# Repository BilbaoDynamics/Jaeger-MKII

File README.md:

# Jaeger MKII

## What's this?

An open source Micro rover robot

## License

GPL license or Creative Commons Attribution-shareAlike (Copyleft)

![license] (http://es.creativecommons.org/blog/wp-content/uploads/2013/04/by-sa_petit.png)

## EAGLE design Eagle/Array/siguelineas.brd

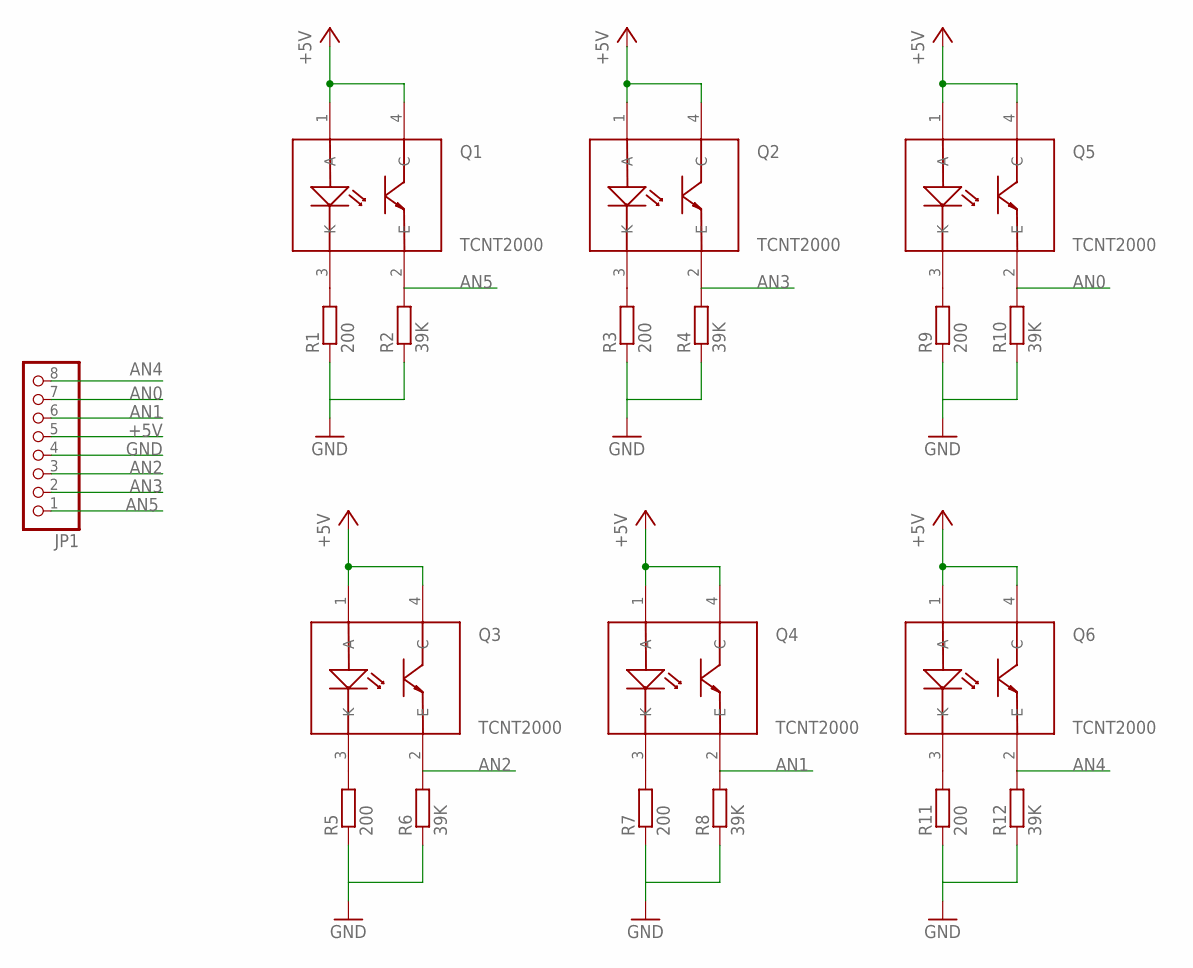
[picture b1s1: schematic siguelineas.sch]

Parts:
JP1: PINHD-1X8; 1X08
Q1, Q2, Q3, Q4, Q5, Q6: TCNT2000; SMD
R1, R3, R5, R7, R9, R11: 200; R0805
R2, R4, R6, R8, R10, R12: 39K; R0805

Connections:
+5V: JP1.5, Q1.1 (A), Q1.4 (C), Q2.1 (A), Q2.4 (C), Q3.1 (A), Q3.4 (C), Q4.1 (A), Q4.4 (C), Q5.1 (A), Q5.4 (C), Q6.1 (A), Q6.4 (C)
AN0: JP1.7, Q5.2 (E), R10.2
AN1: JP1.6, Q4.2 (E), R8.2
AN2: JP1.3, Q3.2 (E), R6.2
AN3: JP1.2, Q2.2 (E), R4.2
AN4: JP1.8, Q6.2 (E), R12.2
AN5: JP1.1, Q1.2 (E), R2.2
GND: JP1.4, R1.1, R2.1, R3.1, R4.1, R5.1, R6.1, R7.1, R8.1, R9.1, R10.1, R11.1, R12.1
unnamed: Q1.3 (K), R1.2
unnamed: Q2.3 (K), R3.2
unnamed: Q3.3 (K), R5.2
unnamed: Q4.3 (K), R7.2
unnamed: Q5.3 (K), R9.2
unnamed: Q6.3 (K), R11.2

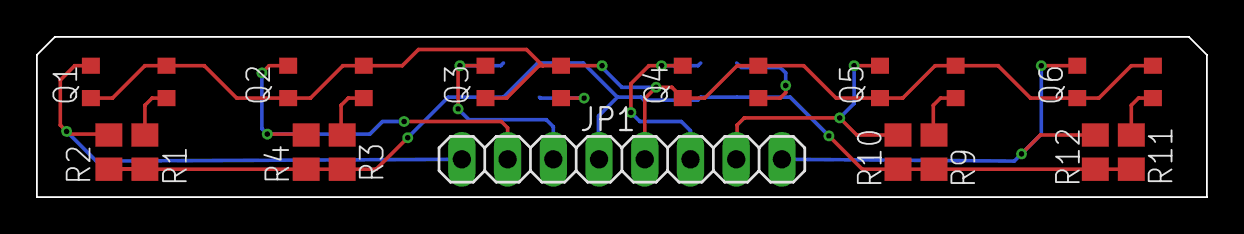
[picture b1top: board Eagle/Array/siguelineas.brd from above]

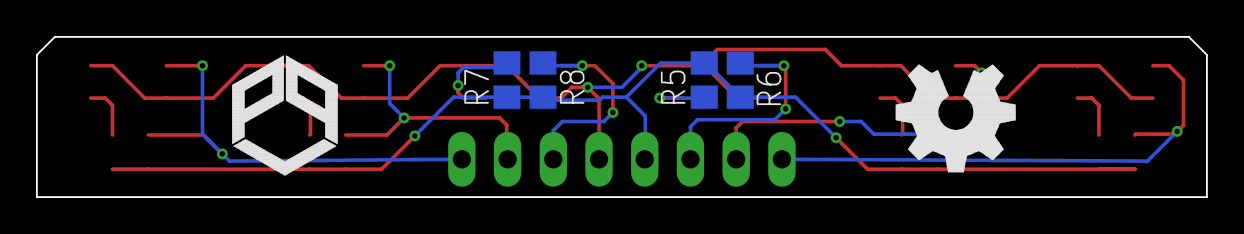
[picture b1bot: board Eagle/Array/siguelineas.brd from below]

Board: 2 copper layers, 65.0 x 8.9 mm, 19 parts (4 on the bottom side), 14 nets.

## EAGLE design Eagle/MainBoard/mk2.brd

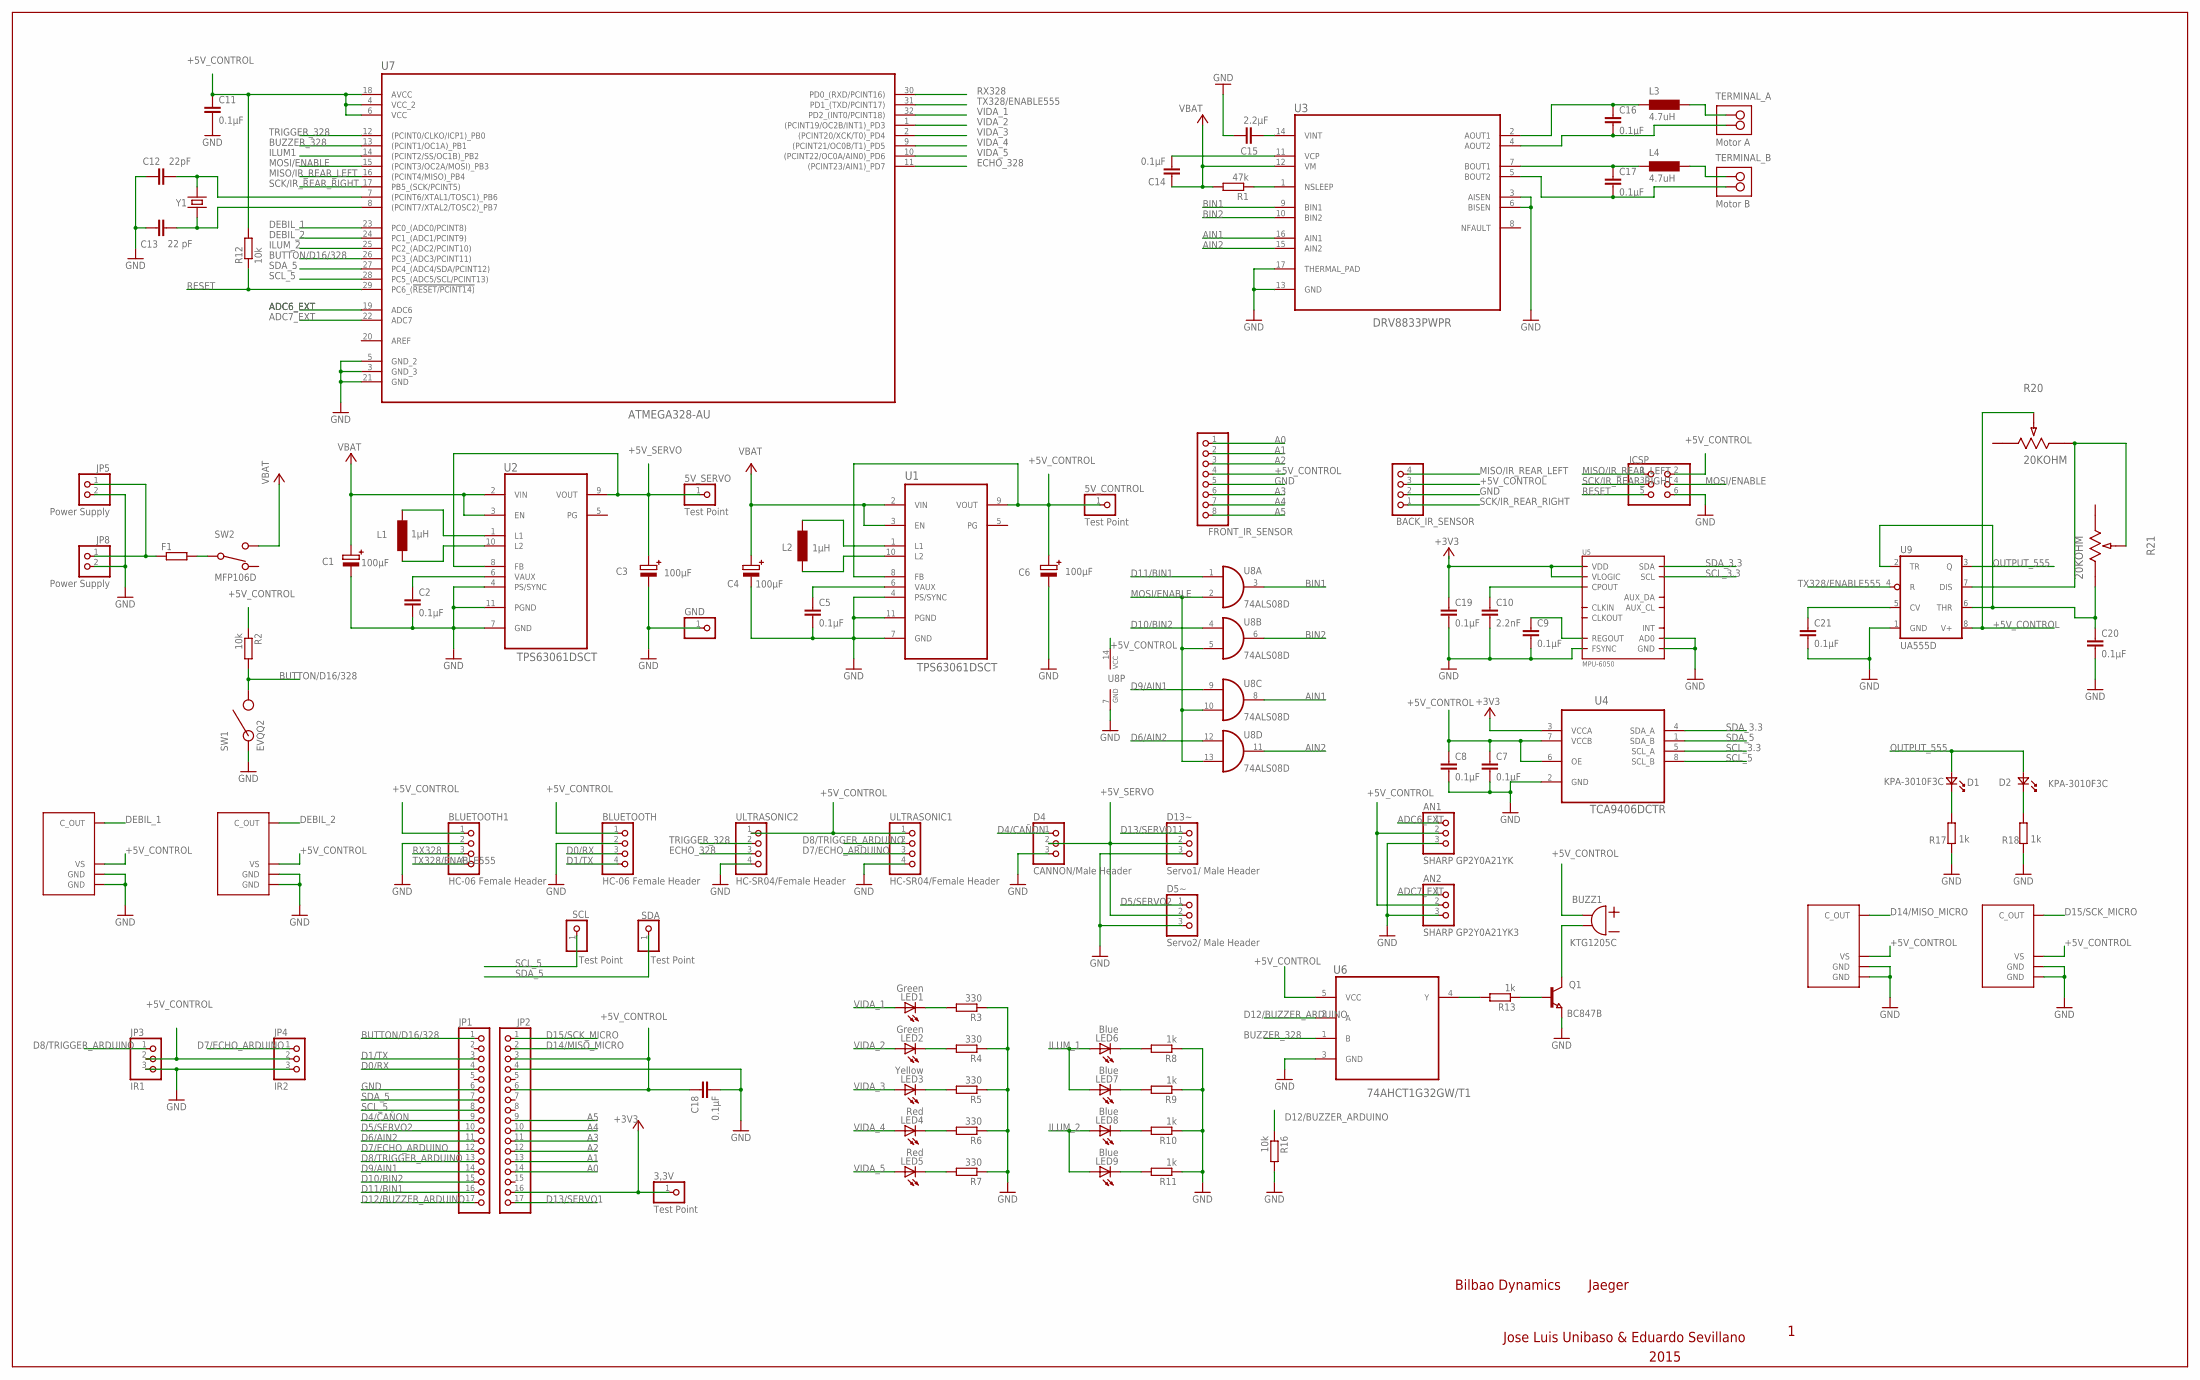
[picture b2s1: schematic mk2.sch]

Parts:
3,3V, 5V_CONTROL, 5V_SERVO: Test Point; 1X01
AN1: SHARP GP2Y0A21YK; 1X03
AN2: SHARP GP2Y0A21YK3; 1X03
BACK_IR_SENSOR: PINHD-1X4; 1X04
BLUETOOTH, BLUETOOTH1: HC-06 Female Header; 1X04
BUZZ1: KTG1205C
C1, C3, C4, C6: 100µF; EDK107M016A9G
C2, C5, C11: 0.1µF; C0805K
C7, C8, C9, C14, C16, C17, C18, C19, C20, C21: 0.1µF; C0805
C10: 2.2nF; C0805
C12: 22pF; C0805K
C13: 22 pF; C0805K
C15: 2.2µF; C0805
D1, D2: KPA-3010F3C
D4: CANNON/Male Header; 1X03
D5~: Servo2/ Male Header; 1X03
D13~: Servo1/ Male Header; 1X03
F1: R-EU_R1206; R1206
FRONT_IR_SENSOR: PINHD-1X8; 1X08
GND: PINHD-1X1; 1X01
ICSP: PINHD-2X3; 2X03
IR_REC1, IR_REC2, IR_REC3, IR_REC4: TSMP77000TR
JP1, JP2: PINHD-1X17; 1X17
JP3: IR1; 1X03
JP4: IR2; 1X03
JP5, JP8: Power Supply; 1X02
L1, L2: 1µH; MCSDRH73B
L3, L4: 4.7uH; SRN4012T-4R7M
LED1, LED2: Green; SML0805
LED3: Yellow; SML0805
LED4, LED5: Red; SML0805
LED6, LED7, LED8, LED9: Blue; SML0805
Q1: BC847B; SOT23
R1: 47k; R0805
R2, R12, R16: 10k; R0805
R3, R4, R5, R6, R7: 330; R0805
R8, R9, R10, R11, R13, R17, R18: 1k; R0805
R20, R21: 20KOHM; POT_EVM2N
SCL: Test Point; 1X01
SDA: Test Point; 1X01
SW1: EVQQ2
SW2: MFP106D
TERMINAL_A: Motor A; CTB30512BK
TERMINAL_B: Motor B; CTB30512BK
U1, U2: TPS63061DSCT; SON50P300X300X80-11N
U3: DRV8833PWPR; SOP65P640X120-17N
U4: TCA9406DCTR; SOP65P400X130-8N
U5: MPU-6050; QFN.24.4X4
U6: 74AHCT1G32GW/T1; SOT65P210X110-5N
U7: ATMEGA328-AU; QFP80P900X900X120-32N
U8: 74ALS08D; SO14
U9: UA555D; SO08
ULTRASONIC1, ULTRASONIC2: HC-SR04/Female Header; 1X04
Y1: E3SB16.0000F09G11AE; E3SB16.0000F09G11A

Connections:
+3V3: 3,3V.1, JP2.16, U4.3 (VCCA)
+5V_CONTROL: 5V_CONTROL.1, AN1.2, AN2.2, BACK_IR_SENSOR.3, BLUETOOTH.1, BLUETOOTH1.1, BUZZ1.+, C6.1, C7.1, C8.1, C11.1, C18.1, FRONT_IR_SENSOR.4, ICSP.2, IR_REC1.2 (VS), IR_REC2.2 (VS), IR_REC3.2 (VS), IR_REC4.2 (VS), JP2.3, JP2.6, JP3.2, JP4.2, R2.1, R12.2, R20.2, U1.8 (FB), U1.9 (VOUT), U4.6 (OE), U4.7 (VCCB), U6.5 (VCC), U7.4 (VCC_2), U7.6 (VCC), U7.18 (AVCC), U8.14 (VCC), U9.8 (V+), ULTRASONIC1.1, ULTRASONIC2.1
+5V_SERVO: 5V_SERVO.1, C3.1, D4.2, D5~.2, D13~.2, U2.8 (FB), U2.9 (VOUT)
A0: FRONT_IR_SENSOR.1, JP2.14
A1: FRONT_IR_SENSOR.2, JP2.13
A2: FRONT_IR_SENSOR.3, JP2.12
A3: FRONT_IR_SENSOR.6, JP2.11
A4: FRONT_IR_SENSOR.7, JP2.10
A5: FRONT_IR_SENSOR.8, JP2.9
ADC6_EXT: AN1.1, U7.19 (ADC6)
ADC7_EXT: AN2.1, U7.22 (ADC7)
AIN1: U3.16 (AIN1), U8.8 (O)
AIN2: U3.15 (AIN2), U8.11 (O)
AM1: L3.P$2, TERMINAL_A.1
BIN1: U3.9 (BIN1), U8.3 (O)
BIN2: U3.10 (BIN2), U8.6 (O)
BM1: L4.P$2, TERMINAL_B.1
BUTTON/D16/328: JP1.1, R2.2, SW1.P$1, SW1.P$4, U7.26 (PC3_(ADC3/PCINT11))
BUZZER_328: U6.1 (B), U7.13 ((PCINT1/OC1A)_PB1)
C14: C13.2, U7.8 ((PCINT7/XTAL2/TOSC2)_PB7), Y1.1
D0/RX: BLUETOOTH.3, JP1.4
D1/TX: BLUETOOTH.4, JP1.3
D2: D2.C, R18.1
D4/CAÑON: D4.1, JP1.9
D5/SERVO2: D5~.1, JP1.10
D6/AIN2: JP1.11, U8.12 (I0)
D7/ECHO_ARDUINO: JP1.12, JP4.1, ULTRASONIC1.3
D8/TRIGGER_ARDUINO: JP1.13, JP3.1, ULTRASONIC1.2
D9/AIN1: JP1.14, U8.9 (I0)
D10/BIN2: JP1.15, U8.4 (I0)
D11/BIN1: JP1.16, U8.1 (I0)
D12/BUZZER_ARDUINO: JP1.17, R16.1, U6.2 (A)
D13/SERVO1: D13~.1, JP2.17
D14/MISO_MICRO: IR_REC1.3 (C_OUT), JP2.2
D15/SCK_MICRO: IR_REC2.3 (C_OUT), JP2.1
DEBIL_1: IR_REC3.3 (C_OUT), U7.23 (PC0_(ADC0/PCINT8))
DEBIL_2: IR_REC4.3 (C_OUT), U7.24 (PC1_(ADC1/PCINT9))
ECHO_328: U7.11 ((PCINT23/AIN1)_PD7), ULTRASONIC2.3
GND: AN1.3, AN2.3, BACK_IR_SENSOR.2, BLUETOOTH.2, BLUETOOTH1.2, C1.2, C2.2, C3.2, C4.2, C5.2, C6.2, C7.2, C8.2, C9.2, C10.2, C11.2, C12.1, C13.1, C15.1, C18.2, C19.2, C20.2, C21.2, D4.3, D5~.3, D13~.3, FRONT_IR_SENSOR.5, GND.1, ICSP.6, IR_REC1.1 (GND), IR_REC1.4 (GND), IR_REC2.1 (GND), IR_REC2.4 (GND), IR_REC3.1 (GND), IR_REC3.4 (GND), IR_REC4.1 (GND), IR_REC4.4 (GND), JP1.6, JP2.4, JP3.3, JP4.3, JP5.2, JP8.2, Q1.2 (E), R3.1, R4.1, R5.1, R6.1, R7.1, R8.1, R9.1, R10.1, R11.1, R16.2, R17.2, R18.2, SW1.P$2, SW1.P$3, U1.4 (PS/SYNC), U1.7 (GND), U1.11 (PGND), U2.4 (PS/SYNC), U2.7 (GND), U2.11 (PGND), U3.3 (AISEN), U3.6 (BISEN), U3.13 (GND), U3.17 (THERMAL_PAD), U4.2 (GND), U5.9 (AD0), U5.11 (FSYNC), U5.18 (GND), U6.3 (GND), U7.3 (GND_3), U7.5 (GND_2), U7.21 (GND), U8.7 (GND), U9.1 (GND), ULTRASONIC1.4, ULTRASONIC2.4
ILUM1: U7.14 ((PCINT2/SS/OC1B)_PB2)
ILUM_1: LED6.A, LED7.A
ILUM_2: LED8.A, LED9.A, U7.25 (PC2_(ADC2/PCINT10))
LED4: LED4.C, R6.2
MISO/IR_REAR_LEFT: BACK_IR_SENSOR.4, ICSP.1, U7.16 ((PCINT4/MISO)_PB4)
MOSI/ENABLE: ICSP.4, U7.15 ((PCINT3/OC2A/MOSI)_PB3), U8.2 (I1), U8.5 (I1), U8.10 (I1), U8.13 (I1)
unnamed: C16.1, L3.P$1, U3.2 (AOUT1)
unnamed: C16.2, TERMINAL_A.2, U3.4 (AOUT2)
unnamed: C17.1, L4.P$1, U3.7 (BOUT1)
unnamed: C17.2, TERMINAL_B.2, U3.5 (BOUT2)
unnamed: C19.1, U5.8 (VLOGIC), U5.13 (VDD)
unnamed: F1.1, JP5.1, JP8.1
unnamed: R1.1, U3.1 (NSLEEP)
unnamed: C14.2, U3.11 (VCP)
unnamed: L2.2, U1.1 (L1)
unnamed: C2.1, U2.6 (VAUX)
unnamed: L2.1, U1.10 (L2)
unnamed: R13.2, U6.4 (Y)
unnamed: Q1.1 (B), R13.1
unnamed: L1.2, U2.1 (L1)
unnamed: L1.1, U2.10 (L2)
unnamed: BUZZ1.-, Q1.3 (C)
unnamed: C5.1, U1.6 (VAUX)
unnamed: LED1.C, R3.2
unnamed: LED2.C, R4.2
unnamed: LED3.C, R5.2
unnamed: LED8.C, R10.2
unnamed: D1.C, R17.1
unnamed: LED5.C, R7.2
unnamed: C15.2, U3.14 (VINT)
unnamed: C12.2, U7.7 ((PCINT6/XTAL1/TOSC1)_PB6), Y1.2
unnamed: C20.1, R21.3, U9.2 (TR), U9.6 (THR)
unnamed: LED6.C, R8.2
unnamed: LED7.C, R9.2
unnamed: LED9.C, R11.2
unnamed: C10.1, U5.20 (CPOUT)
unnamed: C9.1, U5.10 (REGOUT)
unnamed: R20.3, R21.2, U9.7 (DIS)
unnamed: F1.2, SW2.COM
unnamed: C21.1, U9.5 (CV)
OUTPUT_555: D1.A, D2.A, U9.3 (Q)
RESET: ICSP.5, R12.1, U7.29 (PC6_(!RESET/PCINT14))
RX328: BLUETOOTH1.3, U7.30 (PD0_(RXD/PCINT16))
SCK/IR_REAR_RIGHT: BACK_IR_SENSOR.1, ICSP.3, U7.17 (PB5_(SCK/PCINT5))
SCL_3.3: U4.5 (SCL_A), U5.23 (SCL)
SCL_5: JP1.8, SCL.1, U4.8 (SCL_B), U7.28 (PC5_(ADC5/SCL/PCINT13))
SDA_3.3: U4.4 (SDA_A), U5.24 (SDA)
SDA_5: JP1.7, SDA.1, U4.1 (SDA_B), U7.27 (PC4_(ADC4/SDA/PCINT12))
TRIGGER_328: U7.12 ((PCINT0/CLKO/ICP1)_PB0), ULTRASONIC2.2
TX328/ENABLE555: BLUETOOTH1.4, U7.31 (PD1_(TXD/PCINT17)), U9.4 (R)
VBAT: C1.1, C4.1, C14.1, R1.2, SW2.2, U1.2 (VIN), U1.3 (EN), U2.2 (VIN), U2.3 (EN), U3.12 (VM)
VIDA_1: LED1.A, U7.32 (PD2_(INT0/PCINT18))
VIDA_2: LED2.A, U7.1 ((PCINT19/OC2B/INT1)_PD3)
VIDA_3: LED3.A, U7.2 ((PCINT20/XCK/T0)_PD4)
VIDA_4: LED4.A, U7.9 ((PCINT21/OC0B/T1)_PD5)
VIDA_5: LED5.A, U7.10 ((PCINT22/OC0A/AIN0)_PD6)

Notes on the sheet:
Bilbao Dynamics
Jaeger
Jose Luis Unibaso & Eduardo Sevillano
2015

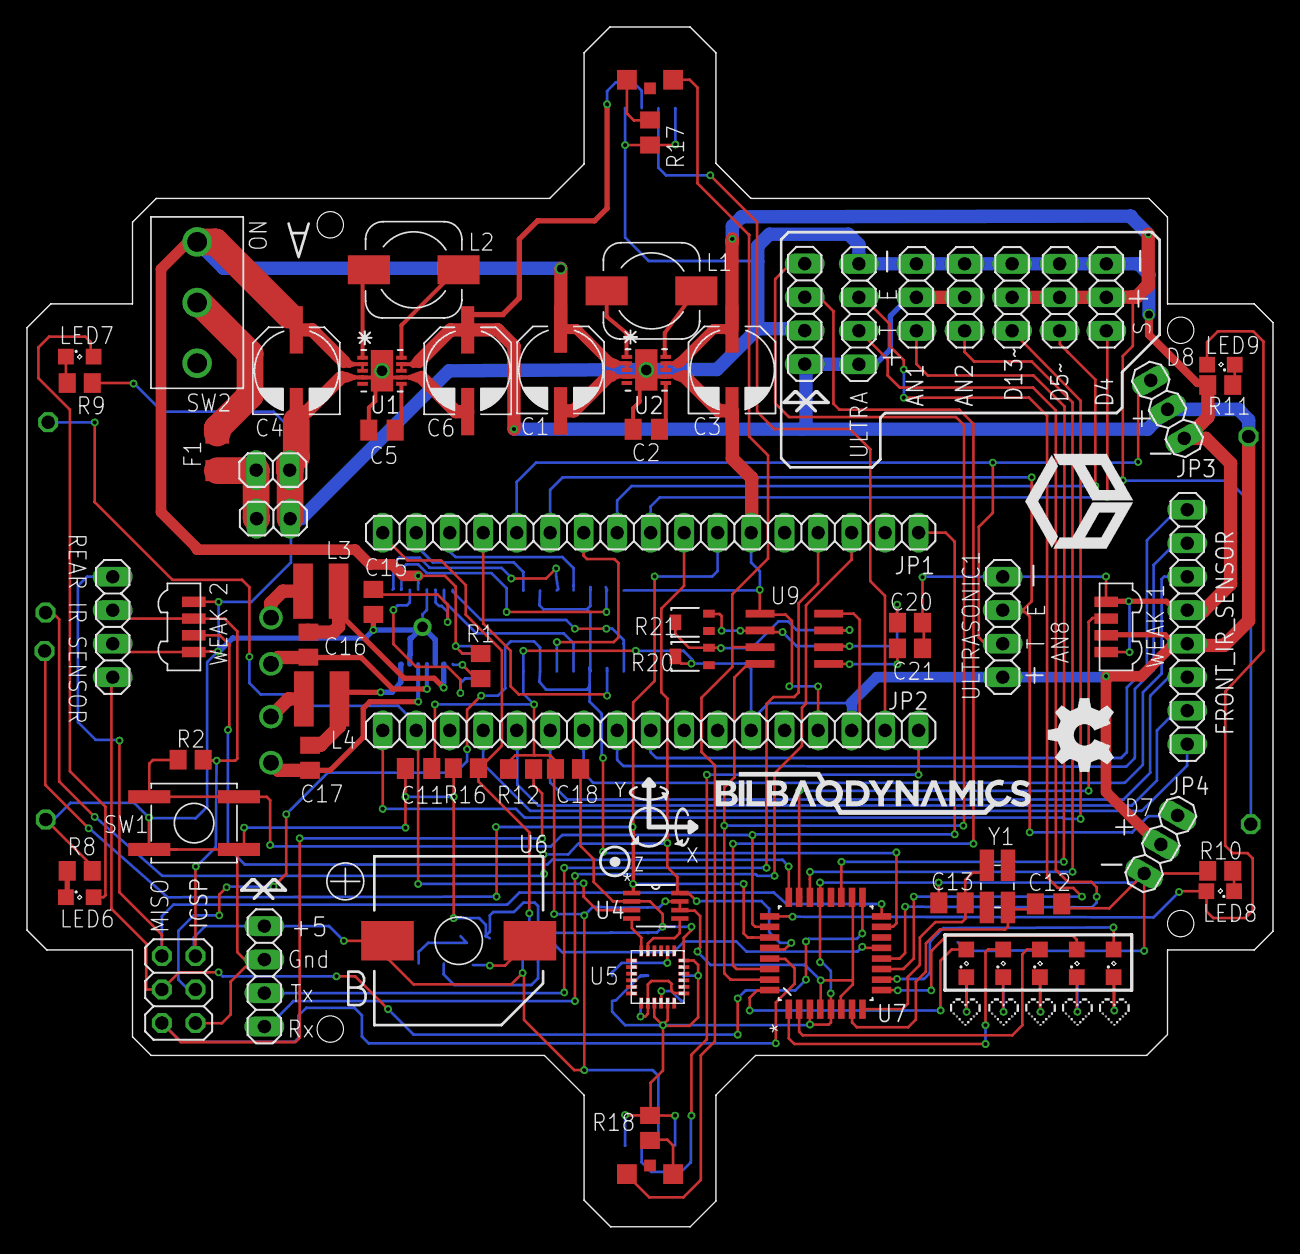
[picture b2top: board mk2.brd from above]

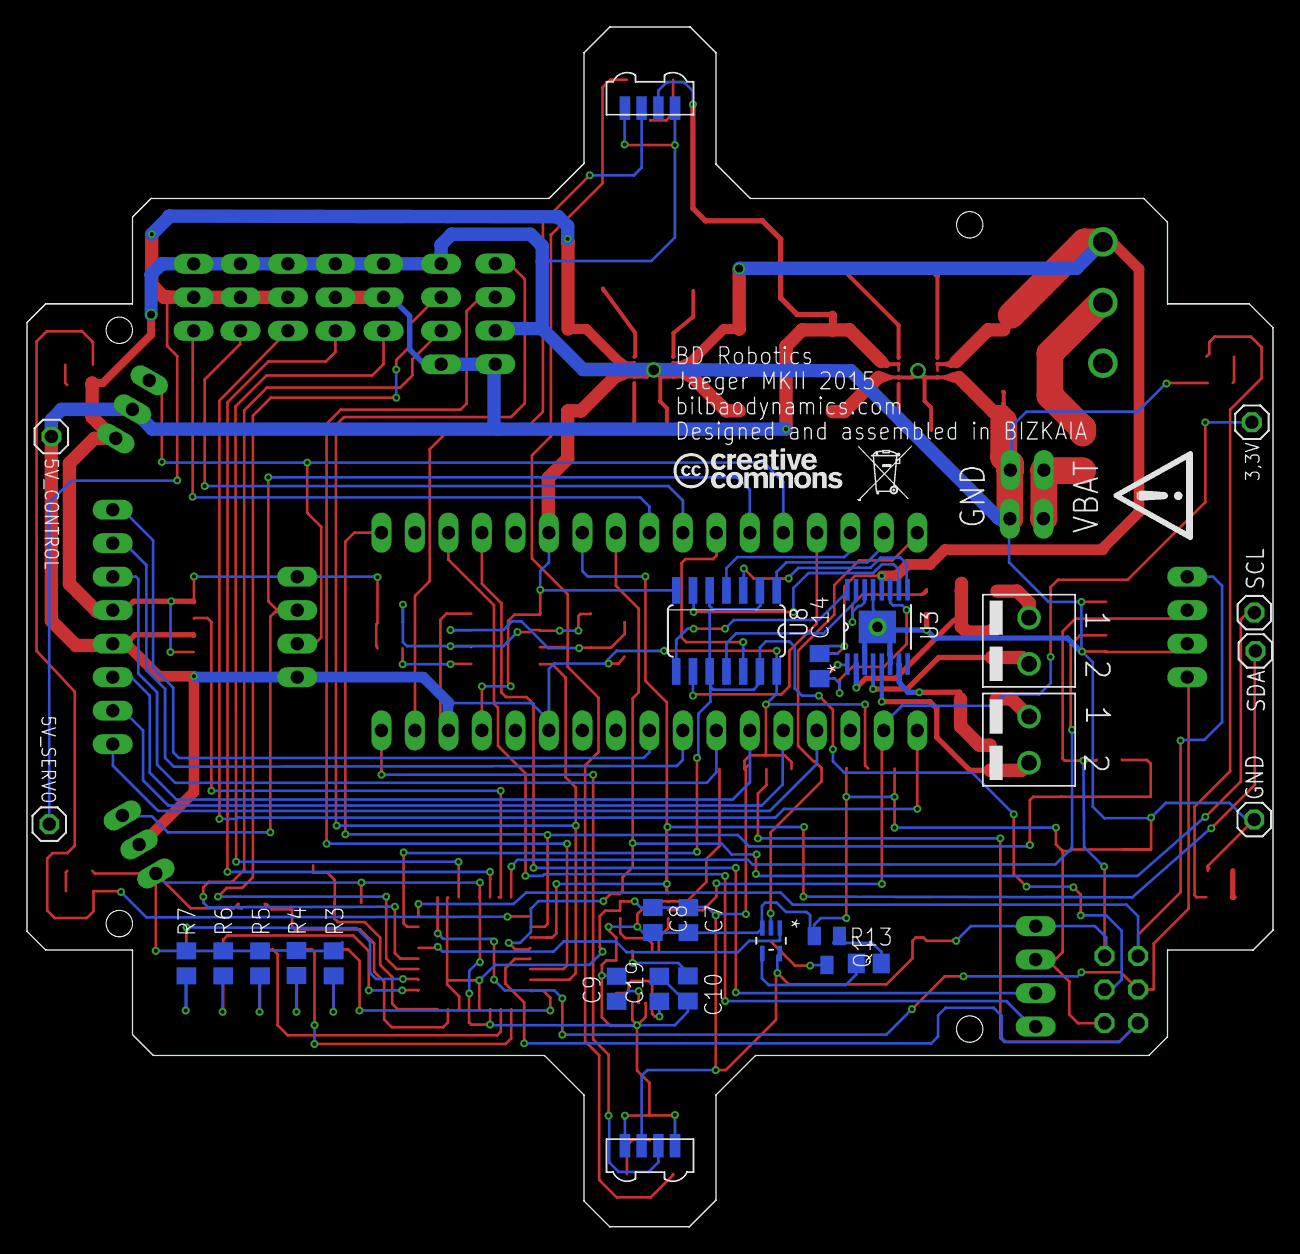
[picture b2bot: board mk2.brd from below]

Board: 2 copper layers, 94.5 x 91.0 mm, 99 parts (24 on the bottom side), 94 nets.

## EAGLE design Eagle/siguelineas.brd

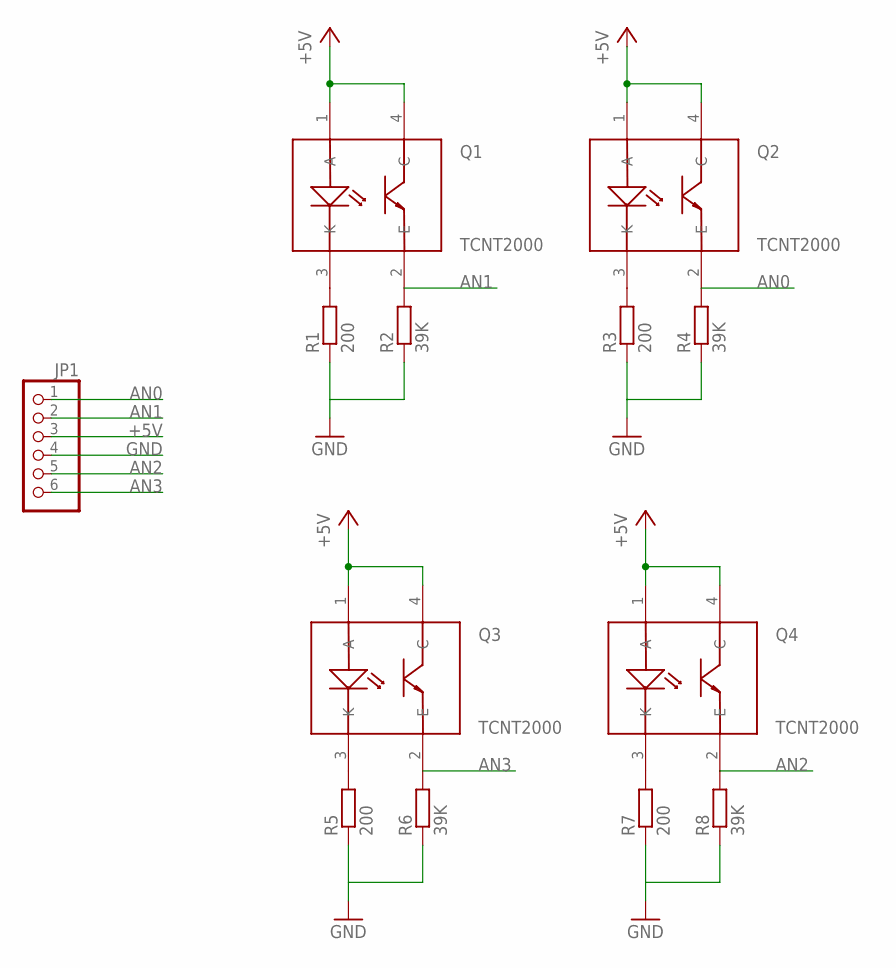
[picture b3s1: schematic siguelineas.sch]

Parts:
JP1: PINHD-1X6; 1X06
Q1, Q2, Q3, Q4: TCNT2000; SMD
R1, R3, R5, R7: 200; R0805
R2, R4, R6, R8: 39K; R0805

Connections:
+5V: JP1.3, Q1.1 (A), Q1.4 (C), Q2.1 (A), Q2.4 (C), Q3.1 (A), Q3.4 (C), Q4.1 (A), Q4.4 (C)
AN0: JP1.1, Q2.2 (E), R4.2
AN1: JP1.2, Q1.2 (E), R2.2
AN2: JP1.5, Q4.2 (E), R8.2
AN3: JP1.6, Q3.2 (E), R6.2
GND: JP1.4, R1.1, R2.1, R3.1, R4.1, R5.1, R6.1, R7.1, R8.1
unnamed: Q1.3 (K), R1.2
unnamed: Q2.3 (K), R3.2
unnamed: Q3.3 (K), R5.2
unnamed: Q4.3 (K), R7.2

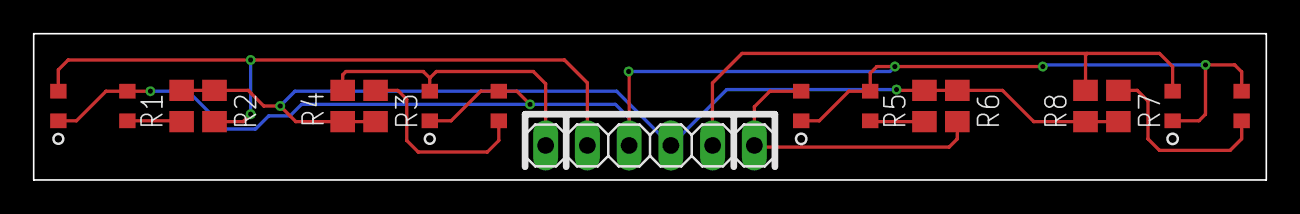
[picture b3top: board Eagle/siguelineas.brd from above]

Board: 2 copper layers, 75.0 x 8.9 mm, 13 parts (0 on the bottom side), 10 nets.

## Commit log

2015-11-05 File update
2015-11-17 Eagle Folder
2015-12-17 update
    files
